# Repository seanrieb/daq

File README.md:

# daq
Data Acquisition Board

Add SparkFun to Arduino IDE board Manager URLs:

https://raw.githubusercontent.com/sparkfun/Arduino_Boards/main/IDE_Board_Manager/package_sparkfun_index.json

Board will be the Pro Micro

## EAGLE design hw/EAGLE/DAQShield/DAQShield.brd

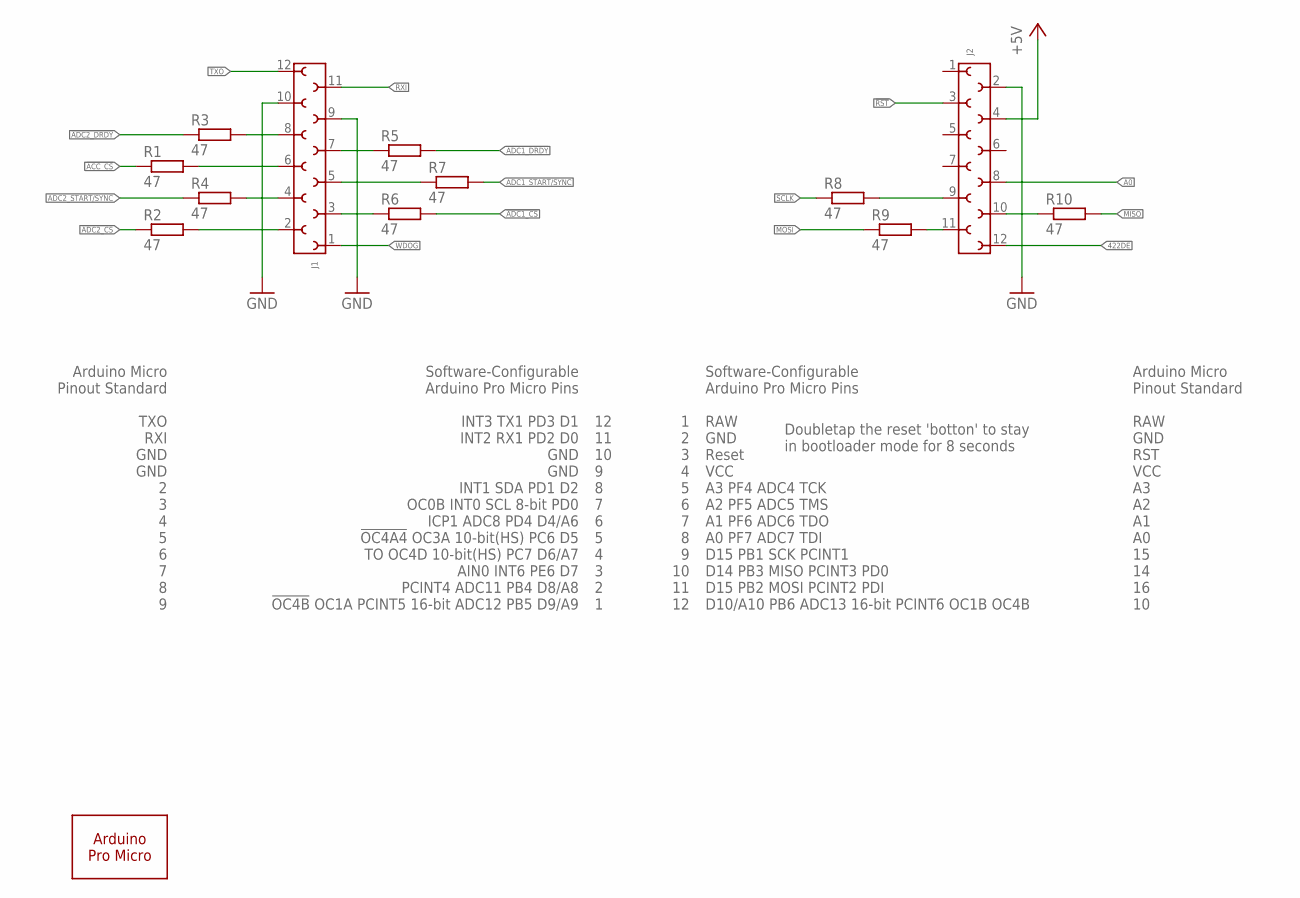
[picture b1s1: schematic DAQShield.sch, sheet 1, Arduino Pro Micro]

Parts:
A1: ARDUINO_PRO_MICRO
J1, J2: 6100XX13321_61001213321; 61001213321
R1, R2, R3, R4, R5, R6, R7, R8, R9, R10: 47; R0603

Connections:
422DE: J2.12; also elsewhere on the board
!ACC_CS: R1.1; also elsewhere on the board
!ADC1_CS: R6.2; also elsewhere on the board
!ADC1_DRDY: R5.2; also elsewhere on the board
!ADC2_CS: R2.1; also elsewhere on the board
!ADC2_DRDY: R3.1; also elsewhere on the board
!RST: J2.3; also elsewhere on the board
+5V: J2.4; also elsewhere on the board
A0: J2.8; also elsewhere on the board
ADC1_START/SYNC: R7.2; also elsewhere on the board
ADC2_START/SYNC: R4.1; also elsewhere on the board
GND: J1.9, J1.10, J2.2; also elsewhere on the board
MISO: R10.2; also elsewhere on the board
MOSI: R9.1; also elsewhere on the board
unnamed: J2.9, R8.2
unnamed: J2.11, R9.2
unnamed: J2.10, R10.1
unnamed: J1.8, R3.2
unnamed: J1.7, R5.1
unnamed: J1.4, R4.2
unnamed: J1.2, R2.2
unnamed: J1.5, R7.1
unnamed: J1.3, R6.1
unnamed: J1.6, R1.2
RXI: J1.11; also elsewhere on the board
SCLK: R8.1; also elsewhere on the board
TXO: J1.12; also elsewhere on the board
WDOG: J1.1; also elsewhere on the board

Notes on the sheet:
Arduino Micro Pinout Standard TXO RXI GND GND 2 3 4 5 6 7 8 9
Software-Configurable Arduino Pro Micro Pins INT3 TX1 PD3 D1 INT2 RX1 PD2 D0 GND GND INT1 SDA PD1 D2 OC0B INT0 SCL 8-bit PD0 ICP1 ADC8 PD4 D4/A6 !OC4A4! OC3A 10-bit(HS) PC6 D5 TO OC4D 10-bit(HS) PC7 D6/A7 AIN0 INT6 PE6 D7 PCINT4 ADC11 PB4 D8/A8 !OC4B! OC1A PCINT5 16-bit ADC12 PB5 D9/A9
12 11 10 9 8 7 6 5 4 3 2 1
1 2 3 4 5 6 7 8 9 10 11 12
Software-Configurable Arduino Pro Micro Pins RAW GND Reset VCC A3 PF4 ADC4 TCK A2 PF5 ADC5 TMS A1 PF6 ADC6 TDO A0 PF7 ADC7 TDI D15 PB1 SCK PCINT1 D14 PB3 MISO PCINT3 PD0 D15 PB2 MOSI PCINT2 PDI D10/A10 PB6 ADC13 16-bit PCINT6 OC1B OC4B
Arduino Micro Pinout Standard RAW GND RST VCC A3 A2 A1 A0 15 14 16 10
Doubletap the reset 'botton' to stay in bootloader mode for 8 seconds

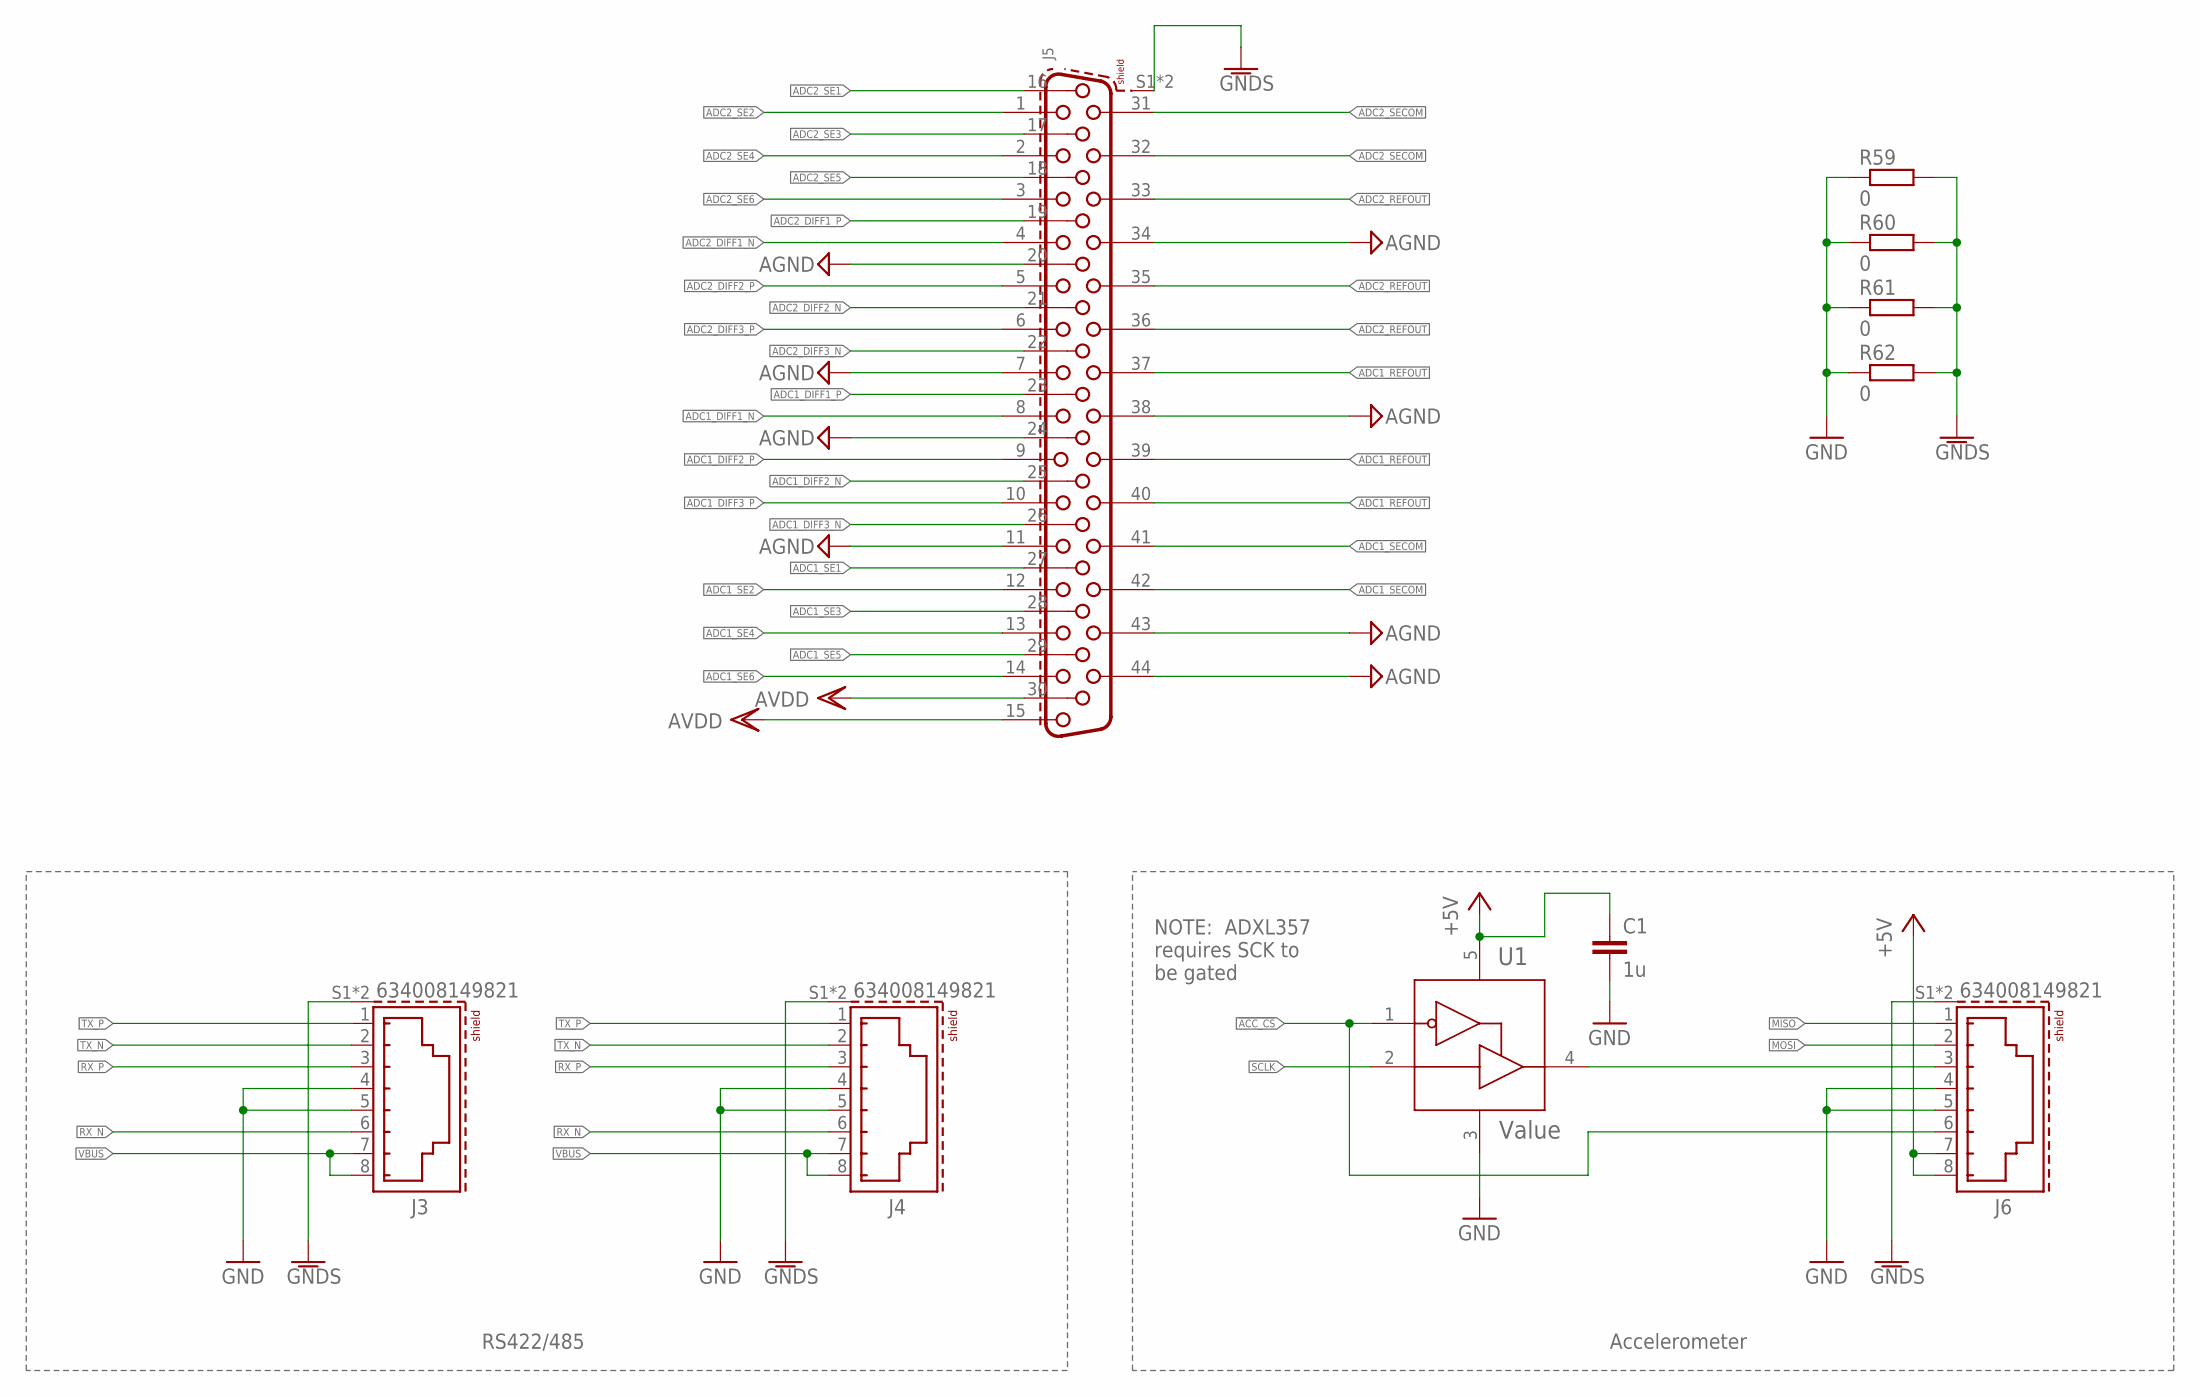
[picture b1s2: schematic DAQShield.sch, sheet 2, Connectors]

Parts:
C1: 1u; C0603
J3, J4, J6: 634008149821
J5: 6180XX330923_618044330923; 618044330923
R59, R60, R61, R62: 0; R1206
U1: Value; DBV0005A_N

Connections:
!ACC_CS: J6.6, U1.1 (OE_N); also elsewhere on the board
+5V: C1.1, J6.7, J6.8, U1.5 (VCC); also elsewhere on the board
ACC_SCLK: J6.3, U1.4 (Y)
ADC1_DIFF1_N: J5.8; also elsewhere on the board
ADC1_DIFF1_P: J5.23; also elsewhere on the board
ADC1_DIFF2_N: J5.25; also elsewhere on the board
ADC1_DIFF2_P: J5.9; also elsewhere on the board
ADC1_DIFF3_N: J5.26; also elsewhere on the board
ADC1_DIFF3_P: J5.10; also elsewhere on the board
ADC1_REFOUT: J5.37, J5.39, J5.40; also elsewhere on the board
ADC1_SE1: J5.27; also elsewhere on the board
ADC1_SE2: J5.12; also elsewhere on the board
ADC1_SE3: J5.28; also elsewhere on the board
ADC1_SE4: J5.13; also elsewhere on the board
ADC1_SE5: J5.29; also elsewhere on the board
ADC1_SE6: J5.14; also elsewhere on the board
ADC1_SECOM: J5.41, J5.42; also elsewhere on the board
ADC2_DIFF1_N: J5.4; also elsewhere on the board
ADC2_DIFF1_P: J5.19; also elsewhere on the board
ADC2_DIFF2_N: J5.21; also elsewhere on the board
ADC2_DIFF2_P: J5.5; also elsewhere on the board
ADC2_DIFF3_N: J5.22; also elsewhere on the board
ADC2_DIFF3_P: J5.6; also elsewhere on the board
ADC2_REFOUT: J5.33, J5.35, J5.36; also elsewhere on the board
ADC2_SE1: J5.16; also elsewhere on the board
ADC2_SE2: J5.1; also elsewhere on the board
ADC2_SE3: J5.17; also elsewhere on the board
ADC2_SE4: J5.2; also elsewhere on the board
ADC2_SE5: J5.18; also elsewhere on the board
ADC2_SE6: J5.3; also elsewhere on the board
ADC2_SECOM: J5.31, J5.32; also elsewhere on the board
AGND: J5.7, J5.11, J5.20, J5.24, J5.34, J5.38, J5.43, J5.44; also elsewhere on the board
AVDD: J5.15, J5.30; also elsewhere on the board
GND: C1.2, J3.4, J3.5, J4.4, J4.5, J6.4, J6.5, R59.1, R60.1, R61.1, R62.1, U1.3 (GND); also elsewhere on the board
GNDS: J3.S1 (SHIELD), J3.S2 (SHIELD), J4.S1 (SHIELD), J4.S2 (SHIELD), J5.S1 (SHIELD), J5.S2 (SHIELD), J6.S1 (SHIELD), J6.S2 (SHIELD), R59.2, R60.2, R61.2, R62.2
MISO: J6.1; also elsewhere on the board
MOSI: J6.2; also elsewhere on the board
RX_N: J3.6, J4.6; also elsewhere on the board
RX_P: J3.3, J4.3; also elsewhere on the board
SCLK: U1.2 (A); also elsewhere on the board
TX_N: J3.2, J4.2; also elsewhere on the board
TX_P: J3.1, J4.1; also elsewhere on the board
VBUS: J3.7, J3.8, J4.7, J4.8; also elsewhere on the board

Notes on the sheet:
RS422/485
Accelerometer
NOTE: ADXL357 requires SCK to be gated

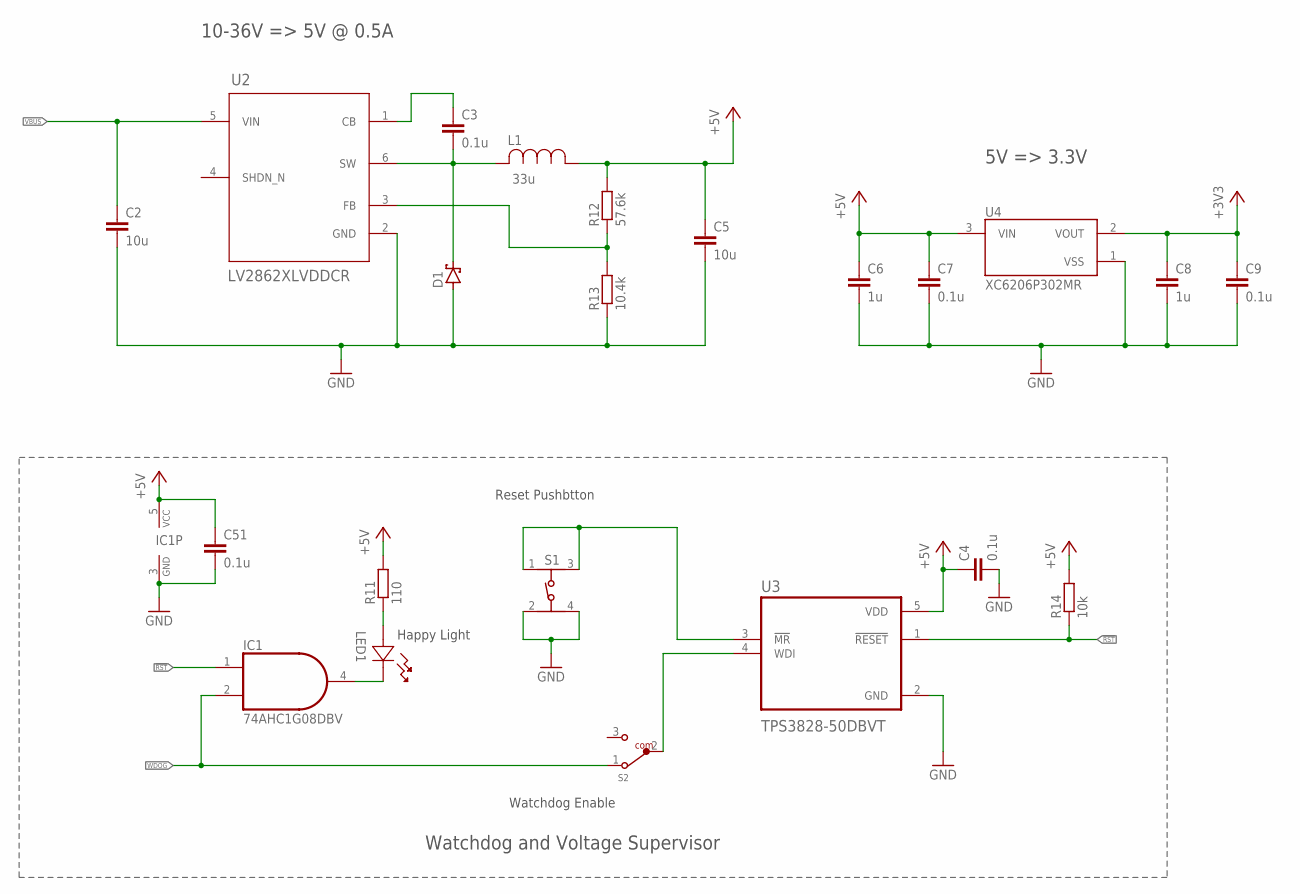
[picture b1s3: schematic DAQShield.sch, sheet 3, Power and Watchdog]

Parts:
C2: 10u; C1210
C3: 0.1u; C0805
C4, C7, C9, C51: 0.1u; C0603
C5: 10u; C0805
C6, C8: 1u; C0603
D1: PMEG6010CEH,115; SOD123FL
IC1: 74AHC1G08DBV; SOT23-5
L1: 33u; IND_BOURNS_SRU8043
LED1: APA1606QBC/D; LED_APA1606_KNB
R11: 110; R0603
R12: 57.6k; R0402
R13: 10.4k; R0805
R14: 10k; R0603
S1: 434153017835
S2: 450404015514
U2: LV2862XLVDDCR; DDC0006A-IPC_A
U3: TPS3828-50DBVT; SOT95P280X145-5N
U4: XC6206P302MR; SOT95P280X130-3N

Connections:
!RST: IC1.1 (I0), R14.1, U3.1 (!RESET); also elsewhere on the board
+3V3: C8.1, C9.1, U4.2 (VOUT); also elsewhere on the board
+5V: C4.1, C5.1, C6.1, C7.1, C51.1, IC1.5 (VCC), L1.1, R11.2, R12.2, R14.2, U3.5 (VDD), U4.3 (VIN); also elsewhere on the board
GND: C2.2, C4.2, C5.2, C6.2, C7.2, C8.2, C9.2, C51.2, D1.A, IC1.3 (GND), R13.1, S1.2 (3), S1.4, U2.2 (GND), U3.2 (GND), U4.1 (VSS); also elsewhere on the board
unnamed: C3.1, U2.1 (CB)
unnamed: C3.2, D1.C, L1.2, U2.6 (SW)
unnamed: R12.1, R13.2, U2.3 (FB)
unnamed: S1.1, S1.3 (2), U3.3 (!MR)
unnamed: S2.2, U3.4 (WDI)
unnamed: IC1.4 (O), LED1.1
unnamed: LED1.2, R11.1
VBUS: C2.1, U2.5 (VIN); also elsewhere on the board
WDOG: IC1.2 (I1), S2.1; also elsewhere on the board

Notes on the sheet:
10-36V => 5V @ 0.5A
Watchdog and Voltage Supervisor
Reset Pushbtton
Watchdog Enable
Happy Light
5V => 3.3V

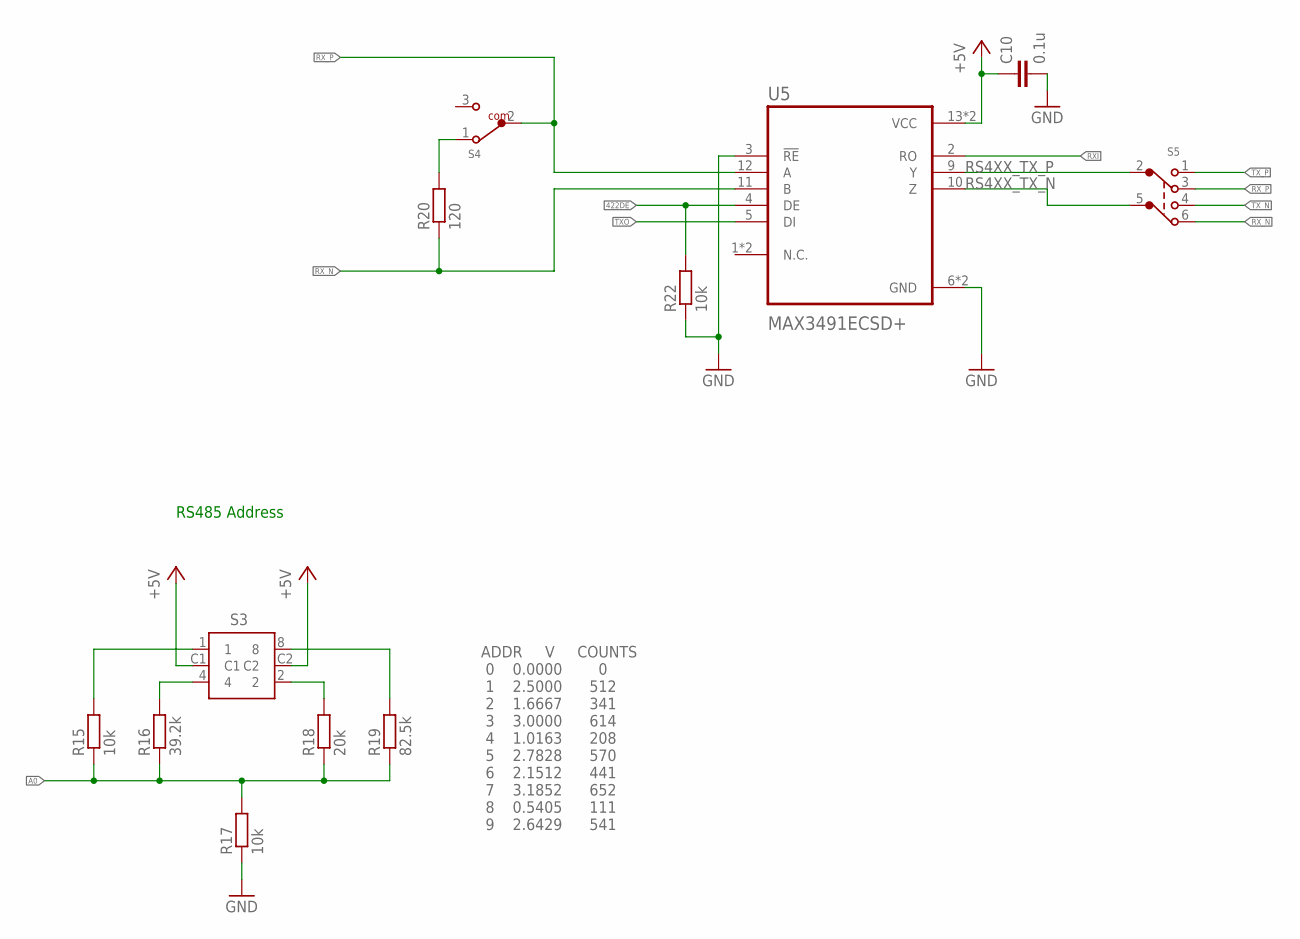
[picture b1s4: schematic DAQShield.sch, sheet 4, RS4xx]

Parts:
C10: 0.1u; C0603
R15, R17, R22: 10k; R0603
R16: 39.2k; R0603
R18: 20k; R0603
R19: 82.5k; R0603
R20: 120; R0603
S3: 428427320910; 42842732091X_10POS
S4: 450404015514
S5: 452403012014
U5: MAX3491ECSD+; SOIC127P600X175-14N

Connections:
422DE: R22.2, U5.4 (DE); also elsewhere on the board
+5V: C10.1, S3.C1, S3.C2, U5.13 (VCC), U5.14 (VCC); also elsewhere on the board
A0: R15.1, R16.1, R17.2, R18.1, R19.1; also elsewhere on the board
GND: C10.2, R17.1, R22.1, U5.3 (!RE), U5.6 (GND), U5.7 (GND); also elsewhere on the board
unnamed: R20.2, S4.1
unnamed: R15.2, S3.1
unnamed: R16.2, S3.4
unnamed: R19.2, S3.8
unnamed: R18.2, S3.2
RS4XX_TX_N: S5.5, U5.10 (Z)
RS4XX_TX_P: S5.2, U5.9 (Y)
RXI: U5.2 (RO); also elsewhere on the board
RX_N: R20.1, S5.6, U5.11 (B); also elsewhere on the board
RX_P: S4.2, S5.3, U5.12 (A); also elsewhere on the board
TXO: U5.5 (DI); also elsewhere on the board
TX_N: S5.4; also elsewhere on the board
TX_P: S5.1; also elsewhere on the board

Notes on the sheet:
RS485 Address
ADDR V COUNTS 0 0.0000 0 1 2.5000 512 2 1.6667 341 3 3.0000 614 4 1.0163 208 5 2.7828 570 6 2.1512 441 7 3.1852 652 8 0.5405 111 9 2.6429 541

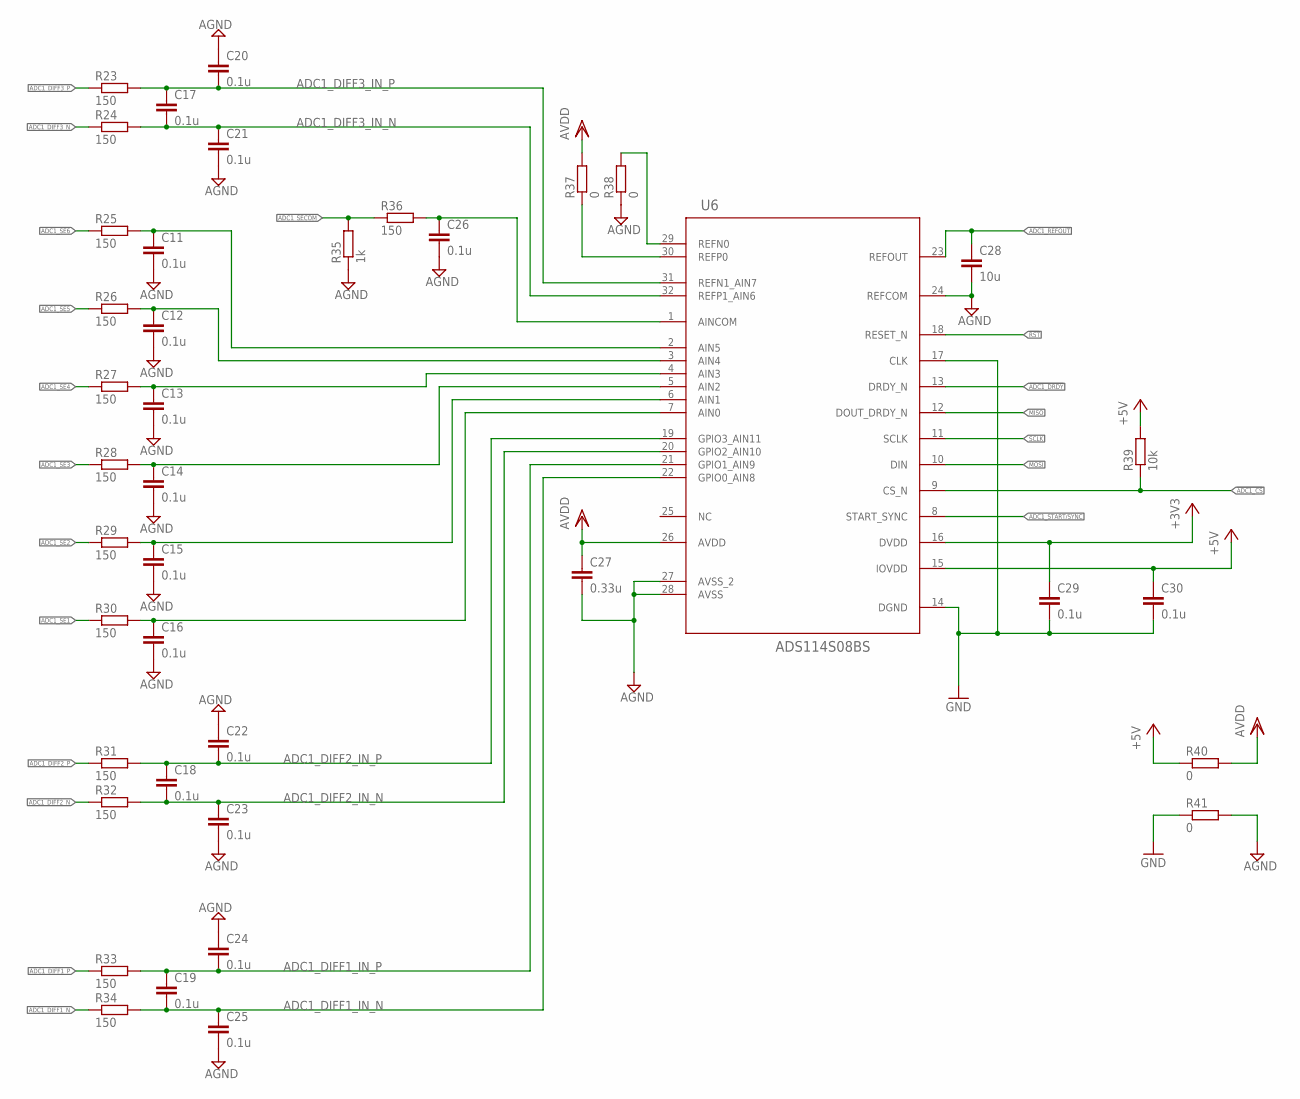
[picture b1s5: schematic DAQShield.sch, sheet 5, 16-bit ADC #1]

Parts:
C11, C12, C13, C14, C15, C16, C17, C18, C19, C20, C21, C22, C23, C24, C25, C26, C29, C30: 0.1u; C0603
C27: 0.33u; C0603
C28: 10u; C0603
R23, R24, R25, R26, R27, R28, R29, R30, R31, R32, R33, R34, R36: 150; R0603
R35: 1k; R0603
R37, R38: 0; R0603
R39: 10k; R0603
R40, R41: 0; R1206
U6: ADS114S08BS; PBS0032A_N

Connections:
!ADC1_CS: R39.1, U6.9 (CS_N); also elsewhere on the board
!ADC1_DRDY: U6.13 (DRDY_N); also elsewhere on the board
!RST: U6.18 (RESET_N); also elsewhere on the board
+3V3: C29.1, U6.16 (DVDD); also elsewhere on the board
+5V: C30.1, R39.2, R40.1, U6.15 (IOVDD); also elsewhere on the board
ADC1_DIFF1_IN_N: C19.2, C25.1, R34.2, U6.22 (GPIO0_AIN8)
ADC1_DIFF1_IN_P: C19.1, C24.2, R33.2, U6.21 (GPIO1_AIN9)
ADC1_DIFF1_N: R34.1; also elsewhere on the board
ADC1_DIFF1_P: R33.1; also elsewhere on the board
ADC1_DIFF2_IN_N: C18.2, C23.1, R32.2, U6.20 (GPIO2_AIN10)
ADC1_DIFF2_IN_P: C18.1, C22.2, R31.2, U6.19 (GPIO3_AIN11)
ADC1_DIFF2_N: R32.1; also elsewhere on the board
ADC1_DIFF2_P: R31.1; also elsewhere on the board
ADC1_DIFF3_IN_N: C17.2, C21.1, R24.2, U6.32 (REFP1_AIN6)
ADC1_DIFF3_IN_P: C17.1, C20.2, R23.2, U6.31 (REFN1_AIN7)
ADC1_DIFF3_N: R24.1; also elsewhere on the board
ADC1_DIFF3_P: R23.1; also elsewhere on the board
ADC1_REFOUT: C28.1, U6.23 (REFOUT); also elsewhere on the board
ADC1_SE1: R30.1; also elsewhere on the board
ADC1_SE2: R29.1; also elsewhere on the board
ADC1_SE3: R28.1; also elsewhere on the board
ADC1_SE4: R27.1; also elsewhere on the board
ADC1_SE5: R26.1; also elsewhere on the board
ADC1_SE6: R25.1; also elsewhere on the board
ADC1_SECOM: R35.2, R36.1; also elsewhere on the board
ADC1_START/SYNC: U6.8 (START_SYNC); also elsewhere on the board
AGND: C11.2, C12.2, C13.2, C14.2, C15.2, C16.2, C20.1, C21.2, C22.1, C23.2, C24.1, C25.2, C26.2, C27.2, C28.2, R35.1, R38.1, R41.2, U6.24 (REFCOM), U6.27 (AVSS_2), U6.28 (AVSS); also elsewhere on the board
AVDD: C27.1, R37.2, R40.2, U6.26 (AVDD); also elsewhere on the board
GND: C29.2, C30.2, R41.1, U6.14 (DGND), U6.17 (CLK); also elsewhere on the board
MISO: U6.12 (DOUT_DRDY_N); also elsewhere on the board
MOSI: U6.10 (DIN); also elsewhere on the board
unnamed: R37.1, U6.30 (REFP0)
unnamed: R38.2, U6.29 (REFN0)
unnamed: C16.1, R30.2, U6.7 (AIN0)
unnamed: C15.1, R29.2, U6.6 (AIN1)
unnamed: C14.1, R28.2, U6.5 (AIN2)
unnamed: C13.1, R27.2, U6.4 (AIN3)
unnamed: C12.1, R26.2, U6.3 (AIN4)
unnamed: C11.1, R25.2, U6.2 (AIN5)
unnamed: C26.1, R36.2, U6.1 (AINCOM)
SCLK: U6.11 (SCLK); also elsewhere on the board

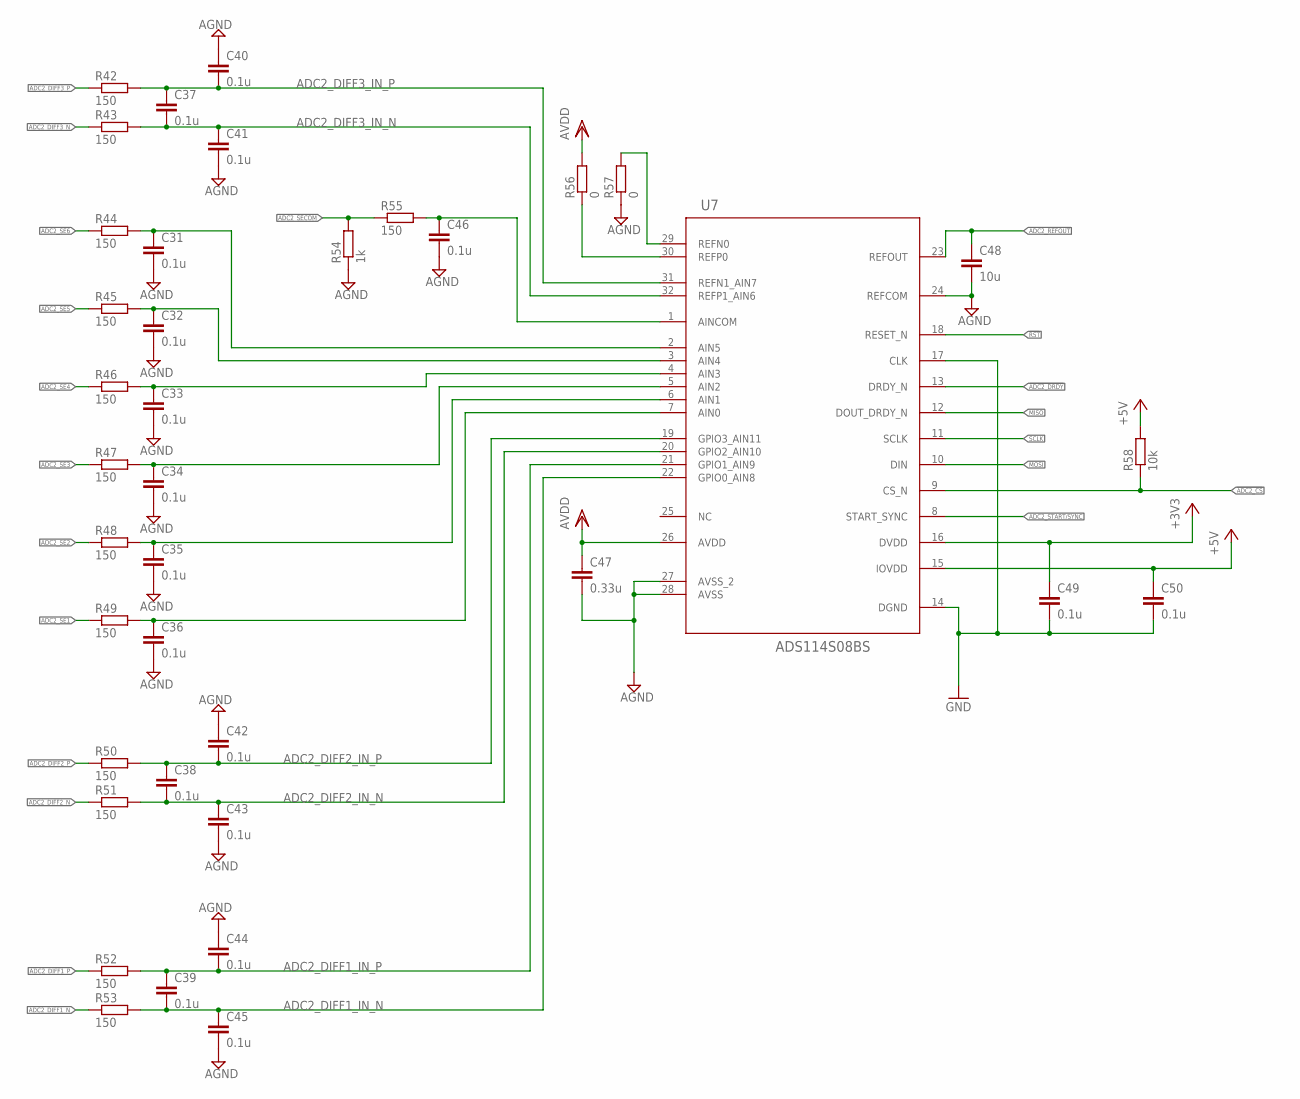
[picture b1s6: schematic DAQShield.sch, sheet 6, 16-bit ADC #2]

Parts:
C31, C32, C33, C34, C35, C36, C37, C38, C39, C40, C41, C42, C43, C44, C45, C46, C49, C50: 0.1u; C0603
C47: 0.33u; C0603
C48: 10u; C0603
R42, R43, R44, R45, R46, R47, R48, R49, R50, R51, R52, R53, R55: 150; R0603
R54: 1k; R0603
R56, R57: 0; R0603
R58: 10k; R0603
U7: ADS114S08BS; PBS0032A_N

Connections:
!ADC2_CS: R58.1, U7.9 (CS_N); also elsewhere on the board
!ADC2_DRDY: U7.13 (DRDY_N); also elsewhere on the board
!RST: U7.18 (RESET_N); also elsewhere on the board
+3V3: C49.1, U7.16 (DVDD); also elsewhere on the board
+5V: C50.1, R58.2, U7.15 (IOVDD); also elsewhere on the board
ADC2_DIFF1_IN_N: C39.2, C45.1, R53.2, U7.22 (GPIO0_AIN8)
ADC2_DIFF1_IN_P: C39.1, C44.2, R52.2, U7.21 (GPIO1_AIN9)
ADC2_DIFF1_N: R53.1; also elsewhere on the board
ADC2_DIFF1_P: R52.1; also elsewhere on the board
ADC2_DIFF2_IN_N: C38.2, C43.1, R51.2, U7.20 (GPIO2_AIN10)
ADC2_DIFF2_IN_P: C38.1, C42.2, R50.2, U7.19 (GPIO3_AIN11)
ADC2_DIFF2_N: R51.1; also elsewhere on the board
ADC2_DIFF2_P: R50.1; also elsewhere on the board
ADC2_DIFF3_IN_N: C37.2, C41.1, R43.2, U7.32 (REFP1_AIN6)
ADC2_DIFF3_IN_P: C37.1, C40.2, R42.2, U7.31 (REFN1_AIN7)
ADC2_DIFF3_N: R43.1; also elsewhere on the board
ADC2_DIFF3_P: R42.1; also elsewhere on the board
ADC2_REFOUT: C48.1, U7.23 (REFOUT); also elsewhere on the board
ADC2_SE1: R49.1; also elsewhere on the board
ADC2_SE2: R48.1; also elsewhere on the board
ADC2_SE3: R47.1; also elsewhere on the board
ADC2_SE4: R46.1; also elsewhere on the board
ADC2_SE5: R45.1; also elsewhere on the board
ADC2_SE6: R44.1; also elsewhere on the board
ADC2_SECOM: R54.2, R55.1; also elsewhere on the board
ADC2_START/SYNC: U7.8 (START_SYNC); also elsewhere on the board
AGND: C31.2, C32.2, C33.2, C34.2, C35.2, C36.2, C40.1, C41.2, C42.1, C43.2, C44.1, C45.2, C46.2, C47.2, C48.2, R54.1, R57.1, U7.24 (REFCOM), U7.27 (AVSS_2), U7.28 (AVSS); also elsewhere on the board
AVDD: C47.1, R56.2, U7.26 (AVDD); also elsewhere on the board
GND: C49.2, C50.2, U7.14 (DGND), U7.17 (CLK); also elsewhere on the board
MISO: U7.12 (DOUT_DRDY_N); also elsewhere on the board
MOSI: U7.10 (DIN); also elsewhere on the board
unnamed: C36.1, R49.2, U7.7 (AIN0)
unnamed: C35.1, R48.2, U7.6 (AIN1)
unnamed: C34.1, R47.2, U7.5 (AIN2)
unnamed: C33.1, R46.2, U7.4 (AIN3)
unnamed: C32.1, R45.2, U7.3 (AIN4)
unnamed: C31.1, R44.2, U7.2 (AIN5)
unnamed: C46.1, R55.2, U7.1 (AINCOM)
unnamed: R57.2, U7.29 (REFN0)
unnamed: R56.1, U7.30 (REFP0)
SCLK: U7.11 (SCLK); also elsewhere on the board

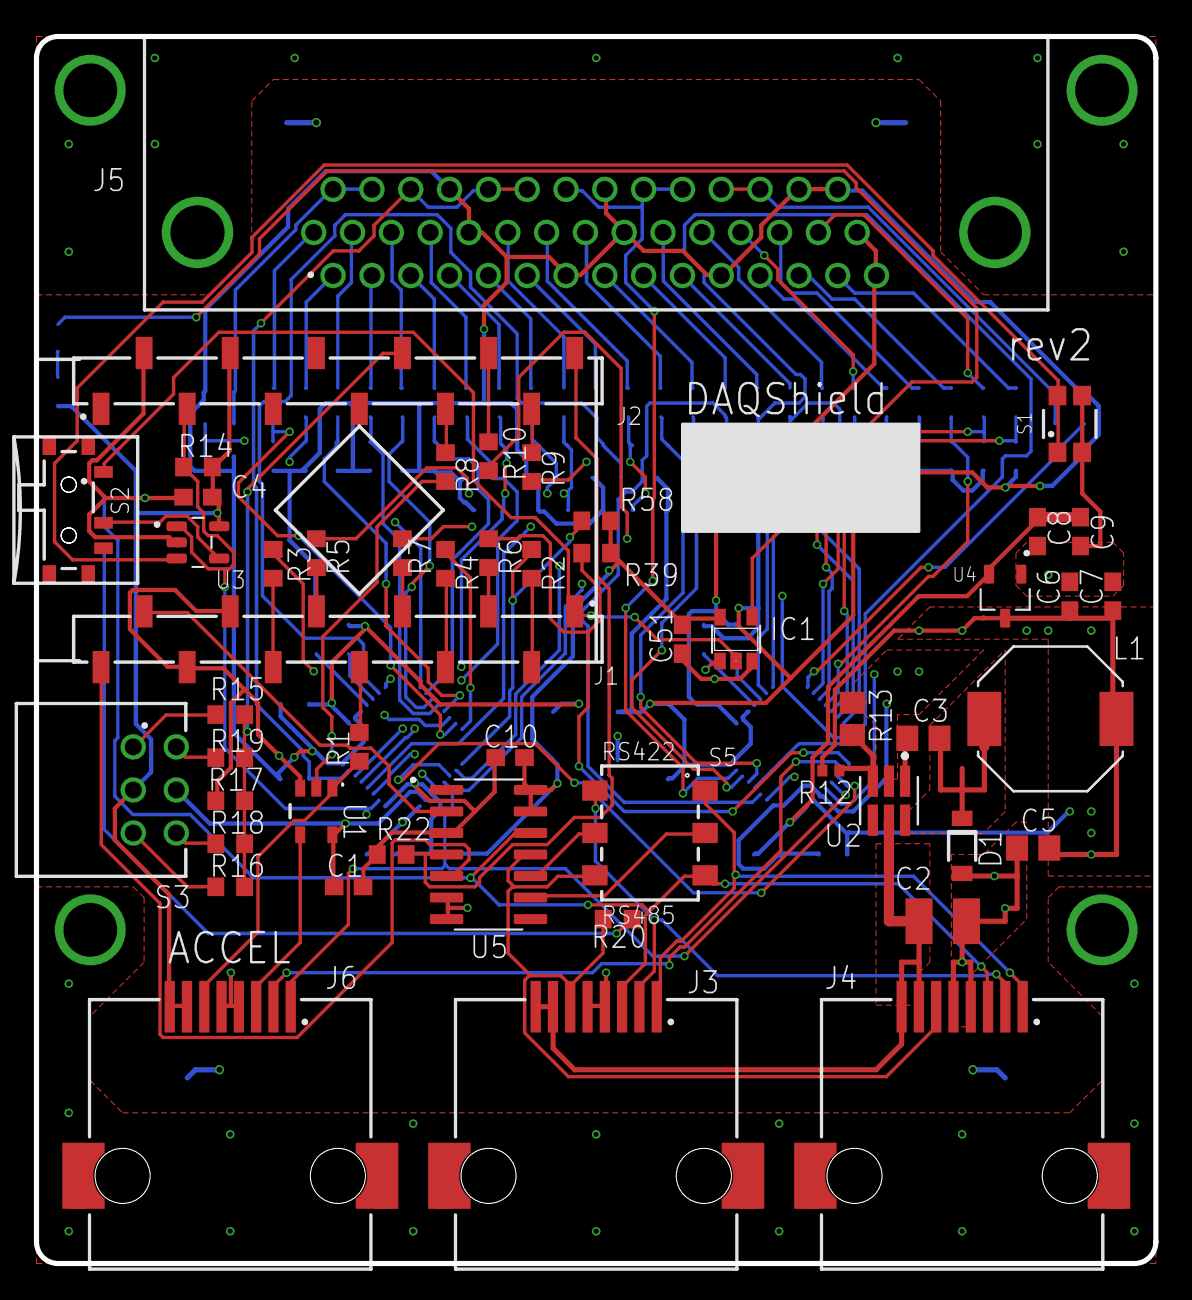
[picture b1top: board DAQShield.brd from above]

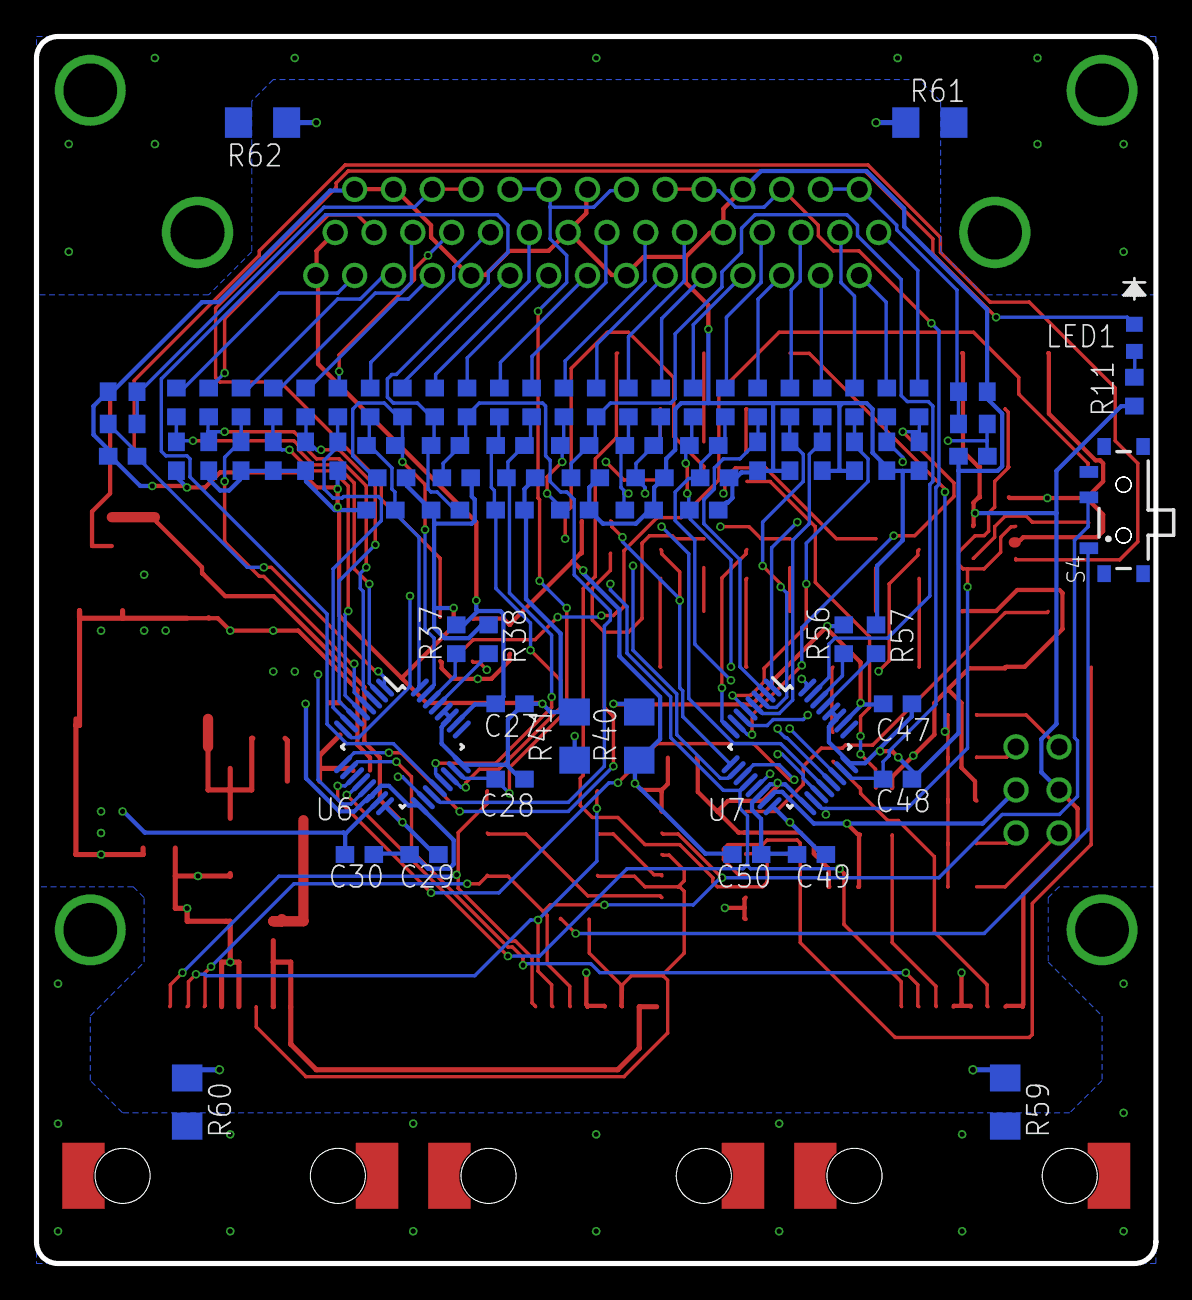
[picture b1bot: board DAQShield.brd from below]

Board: 6 copper layers, 66.0 x 72.4 mm, 135 parts (83 on the bottom side), 110 nets.

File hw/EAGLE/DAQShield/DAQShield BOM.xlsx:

| BUILD | 8
Qty | Onhand | Need | Vendor | Vendor P/N | Value | Device | Package | Parts | Description
1 | 11 | -3 | Amazon |  | ARDUINO_PRO_MICRO | ARDUINO_PRO_MICRO | ARDUINO_PRO_MICRO | A1
3 | 167 | -143 | Mouser | 187-CL10A105KA8NFNC | 1u | C-EUC0603 | C0603 | C1, C6, C8 | CAPACITOR, European symbol
1 | 5 | 3 | Mouser | 963-UMK325C7106MM-T | 10u | C-EUC1210 | C1210 | C2 | CAPACITOR, European symbol
2 | 8 | 8 | Mouser | 187-CL10B334KO8NNNC | 0.33u | C-EUC0603 | C0603 | C27, C47 | CAPACITOR, European symbol
2 | 16 | 0 | Mouser | 963-JMK107ABJ106KA-T | 10u | C-EUC0603 | C0603 | C28, C48 | CAPACITOR, European symbol
1 | 5 | 3 | Mouser | 791-0805B104J500CT | 0.1u | C-EUC0805 | C0805 | C3 | CAPACITOR, European symbol
41 | 734 | -406 | Mouser | 187-CL10B104JB8NNNC | 0.1u | C-EUC0603 | C0603 | C4, C7, C9, C10, C11, C12, C13, C14, C15, C16, C17, C18, C19, C20, C21, C22, C2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 | CAPACITOR, European symbol
1 | 2 | 6 | Mouser | 187-CL31A106MBHNNNE | 10u | C-EUC0805 | C0805 | C5 | CAPACITOR, European symbol
1 | 5 | 3 | Mouser | 771-PMEG6010CEH-T/R | PMEG6010CEH,115 | SMF5.0AT1 | SOD123FL | D1 | 200 W Transient Voltage Suppressor
1 | 8 | 0 | Mouser | 595-SN74LVC08MDBVREP | 74AHC1G08DBV | 74AHC1G08DBV | SOT23-5 | IC1 | 2-input AND gate
2 | 4 | 12 | Mouser | 200-SSM112FSHTR |  | 6100XX13321_61001213321 | 61001213321 | J1, J2 | WR-PHD 2.54 mm SMT Socket Header
3 | 8 | 16 | Mouser | 710-634008149821 | 634008149821 | 634008149821 | 634008149821 | J3, J4, J6 | WR-MJ Modular Jack Horizontal Shielded SMT 8P8C Tab Up
1 | 1 | 7 | Newark | 45X4591 |  | 6180XX330923_618044330923 | 618044330923 | J5 | WR-DSUB Female High Density Angled PCB Connector w. Hex Screw
1 | 5 | 3 | Mouser | 652-SRU8043-330Y | 33u | SRU8043-XXXX | IND_BOURNS_SRU8043 | L1
1 | 6 | 2 | Mouser | 604-APA1606QBC/D | APA1606QBC/D | APA1606QBC/D | LED_APA1606_KNB | LED1
10 | 39 | 41 | Mouser | 71-CRCW060347R0FKEAC | 47 | R-EU_R0603 | R0603 | R1, R2, R3, R4, R5, R6, R7, R8, R9, R10 | RESISTOR, European symbol
1 | 6 | 2 | Mouser | 594-MCT06030C1100FP5 | 110 | R-EU_R0603 | R0603 | R11 | RESISTOR, European symbol
1 | 5 | 3 | Mouser | 603-RT0402FRE0757K6L | 57.6k | R-EU_R0402 | R0402 | R12 | RESISTOR, European symbol
1 | 5 | 3 | Mouser | 603-RT0805BRD0710K4L | 10.4k | R-EU_R0805 | R0805 | R13 | RESISTOR, European symbol
6 | 142 | -94 | Mouser | 603-RT0603FRD0710KL | 10k | R-EU_R0603 | R0603 | R14, R15, R17, R22, R39, R58 | RESISTOR, European symbol
1 | 0 | 8 | Mouser | 756-PCF0603R39K2BI | 39.2k | R-EU_R0603 | R0603 | R16 | RESISTOR, European symbol
1 | 0 | 8 | Mouser | 66-PCFW0603LF032002B | 20k | R-EU_R0603 | R0603 | R18 | RESISTOR, European symbol
1 | 0 | 8 | Mouser | 756-PCF0603R82K5BI | 82.5k | R-EU_R0603 | R0603 | R19 | RESISTOR, European symbol
1 | 35 | -27 | Mouser | 603-RT0603DRE07120RL | 120 | R-EU_R0603 | R0603 | R20 | RESISTOR, European symbol
26 | 114 | 94 | Mouser | 667-ERA-3AED151V | 150 | R-EU_R0603 | R0603 | R23, R24, R25, R26, R27, R28, R29, R30, R31, R32, R33, R34, R36, R42, R43, R44,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 | RESISTOR, European symbol
2 | 17 | -1 | Mouser | 667-ERA-3AEB102V | 1k | R-EU_R0603 | R0603 | R35, R54 | RESISTOR, European symbol
4 | 193 | -161 | Mouser | 603-RC0603JR-070RL | 0 | R-EU_R0603 | R0603 | R37, R38, R56, R57 | RESISTOR, European symbol
6 | 82 | -34 | Mouser | 603-RC1206JR-070RL | 0 | R-EU_R1206 | R1206 | R40, R41, R59, R60, R61, R62 | RESISTOR, European symbol
1 | 5 | 3 | Mouser | 710-434153017835 | 434153017835 | 434153017835 | 434153017835 | S1 | WS-TASV J-Bend SMT Tact Switch 3.5x2.9 mm
2 | 6 | 10 | Mouser | 710-450404015514 |  | 450404015514 | 450404015514 | S2, S4 | WS-SLSU Mini Slide Switch, Same Side Connection Side Push 6.7x2.7 mm
1 | 14 | -6 | Digikey | 428427320910-ND |  | 428427320910 | 42842732091X_10POS | S3 | WS-ROTU THT Rotary Switch Right Angled with Arrow Type Actuator, 2.54 mm Pitch,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
1 | 6 | 2 | Mouser | 710-452403012014 |  | 452403012014 | 452403012014 | S5 | WS-SLSV SMD Mini Slide Switch, Same Side Connection 7.65 x 5.5 mm
1 | 3 | 5 | Texas Instruments | SN74LVC1G125DBVR | Value | 74LVC1G125DBVRE4 | DBV0005A_N | U1
1 | 2 | 6 | Texas Instruments | LV2862XLVDDCT/R | LV2862XLVDDCR | LV2862XLVDDCR | DDC0006A-IPC_A | U2
1 | 7 | 1 | Mouser | 595-TPS3828-50DBVT | TPS3828-50DBVT | TPS3828-50DBVT | SOT95P280X145-5N | U3 | Check prices
1 | 6 | 2 | Mouser | 595-TPS7A0533PDBZT | XC6206P302MR | XC6206P302MR | SOT95P280X130-3N | U4 | Linear Voltage Regulator IC 1 Output 200mA SOT-23 Check prices
1 | 2 | 6 | Mouser | 700-MAX3491ECSD | MAX3491ECSD+ | MAX3491ECSD+ | SOIC127P600X175-14N | U5 | Check prices
2 | 6 | 10 | Mouser | ADS114S08BIPBSR | ADS114S08BS | ADS114S08BIPBS | PBS0032A_N | U6, U7

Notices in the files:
hw/EAGLE/DAQShield/DAQShield.brd:
(C)2003 A. DANNENBERG
parts and their libraries:
WR-MJ: Copyright: Würth Elektronik
COPYRIGHT: Copyright (C) 2018 Accelerated Designs. All rights reserved
